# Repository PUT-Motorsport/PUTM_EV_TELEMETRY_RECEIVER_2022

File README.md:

# PUTM_EV_TELEMETRY_RECEIVER_2022

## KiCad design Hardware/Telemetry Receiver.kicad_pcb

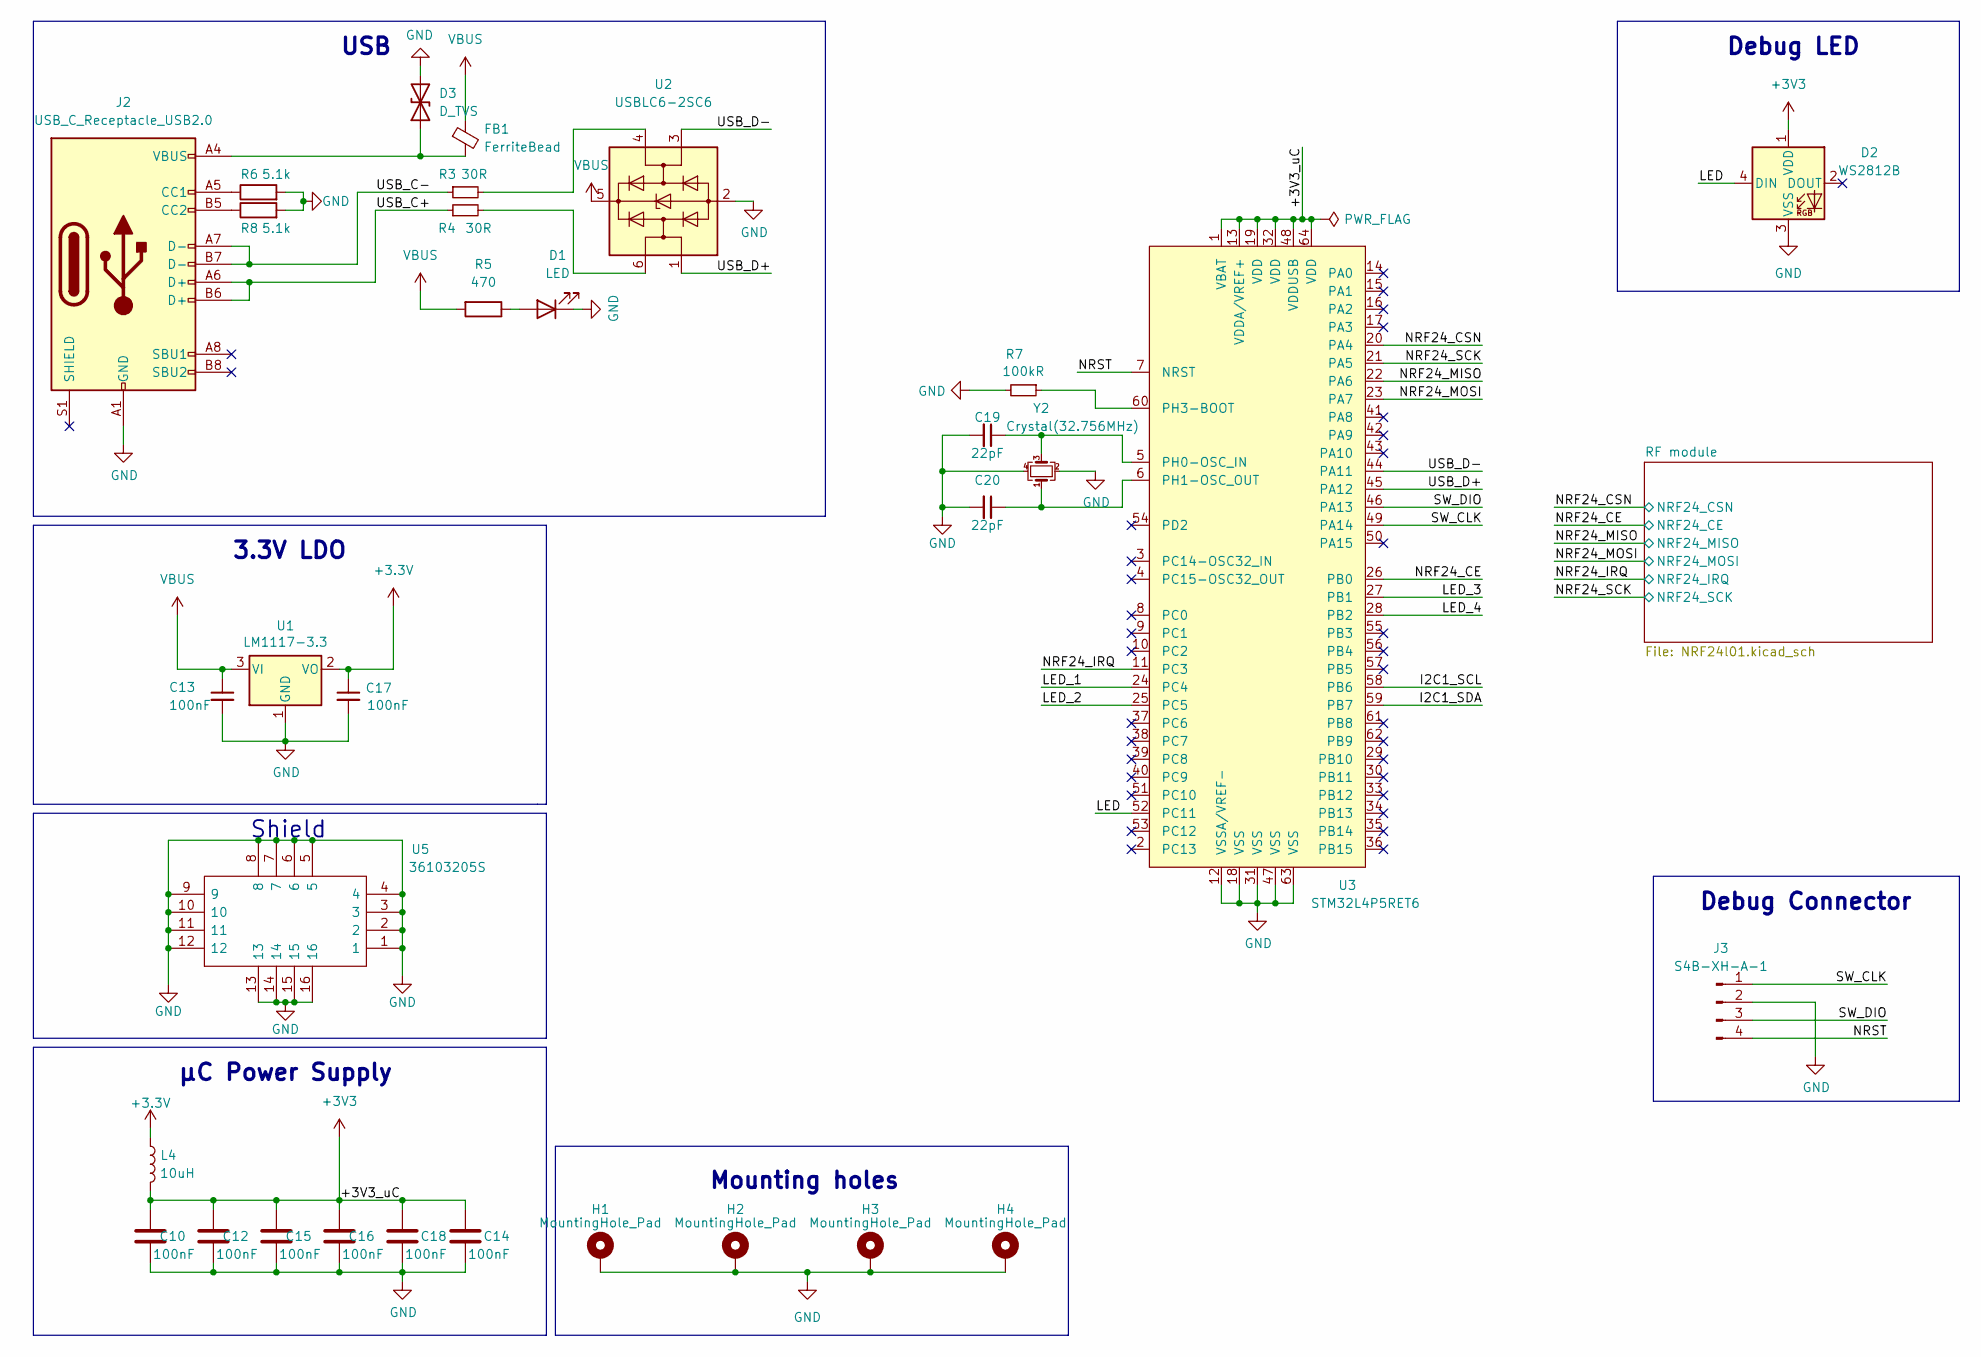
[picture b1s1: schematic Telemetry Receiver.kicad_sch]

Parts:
C10, C12, C13, C14, C15, C16, C17, C18: 100nF; C_0402_1005Metric
C19, C20: 22pF; C_0402_1005Metric; Manufacturer_Part_Number CBR04C220J5GACAUTO; Mouser Part Number 80-CBR04C220J5GAUTO
D1: LED; LED_0603_1608Metric
D2: WS2812B; LED_WS2812B_PLCC4_5.0x5.0mm_P3.2mm
D3: D_TVS; D_0402_1005Metric; Manufacturer_Part_Number LXES02TAA1-144; Mouser Part Number 81-LXES02TAA1-144
FB1: FerriteBead; R_0603_1608Metric; Manufacturer_Part_Number BLM18HE152SH1D; Mouser Part Number 81-BLM18HE152SH1D
H1, H2, H3, H4: MountingHole_Pad; MountingHole_3.2mm_M3_DIN965_Pad
J2: USB_C_Receptacle_USB2.0; USB_C_Receptacle_HRO_TYPE-C-31-M-12; Manufacturer_Part_Number USB4105-GF-A; Mouser Part Number 640-USB4105-GF-A
J3: S4B-XH-A-1; PinSocket_1x04_P2.54mm_Vertical
L4: 10uH; L_0402_1005Metric; Manufacturer_Part_Number LQW15DN100M00D; Mouser Part Number 81-LQW15DN100M00D
R3, R4: 30R; R_0402_1005Metric; Manufacturer_Part_Number 0402WGJ0300TCE; Mouser Part Number SMD0402-30R
R5: 470; R_0402_1005Metric; Manufacturer_Part_Number RN73H1ETTP4700B25; Mouser Part Number 660-RN73H1ETP4700B25
R6, R8: 5.1k; R_0402_1005Metric; Manufacturer_Part_Number RN73H1ETTP5101B25; Mouser Part Number 660-RN73H1ETP5101B25
R7: 100kR; R_0402_1005Metric; Manufacturer_Part_Number RN73H1ETTP1003B50; Mouser Part Number 660-RN73H1ETP1003B50
U1: LM1117-3.3; SOT-223-3_TabPin2
U2: USBLC6-2SC6; SOT-23-6; Manufacturer_Part_Number USBLC6-2SC6; Mouser Part Number USBLC6-2SC6
U3: STM32L4P5RET6
U5: 36103205S; Manufacturer_Part_Number 36103205S; Mouser Part Number 710-36103205S
Y2: Crystal(32.756MHz); Crystal_SMD_2520-4Pin_2.5x2.0mm; Manufacturer_Part_Number FH3200025; Mouser Part Number 729-FH3200025

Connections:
+3.3V: C17.1, L4.1, U1.2 (VO)
+3V3: C10.1, C12.1, C14.1, C15.1, C16.1, C18.1, D2.1 (VDD), L4.2, U3.1 (VBAT), U3.13 (VDDA/VREF+), U3.19 (VDD), U3.32 (VDD), U3.48 (VDDUSB), U3.64 (VDD); also elsewhere on the board
/I2C1_SCL: U3.58 (PB6)
/I2C1_SDA: U3.59 (PB7)
/LED: D2.4 (DIN), U3.52 (PC11)
/LED_1: U3.24 (PC4)
/LED_2: U3.25 (PC5)
/LED_3: U3.27 (PB1)
/LED_4: U3.28 (PB2)
/NRF24_CSN: U3.20 (PA4); also elsewhere on the board
/NRF24_IRQ: U3.11 (PC3); also elsewhere on the board
/NRF24_MISO: U3.22 (PA6); also elsewhere on the board
/NRF24_MOSI: U3.23 (PA7); also elsewhere on the board
/NRF24_SCK: U3.21 (PA5); also elsewhere on the board
/NRST: J3.4, U3.7 (NRST)
/SW_CLK: J3.1, U3.49 (PA14)
/SW_DIO: J3.3, U3.46 (PA13)
/USB_C+: J2.A6 (D+), J2.B6 (D+), R4.1
/USB_C-: J2.A7 (D-), J2.B7 (D-), R3.1
/USB_D+: U2.1 (I/O1), U3.45 (PA12)
/USB_D-: U2.3 (I/O2), U3.44 (PA11)
GND: C10.2, C12.2, C13.2, C14.2, C15.2, C16.2, C17.2, C18.2, C19.2, C20.2, D1.1 (K), D2.3 (VSS), D3.2 (A2), H1.1, H2.1, H3.1, H4.1, J2.A1 (GND), J2.A12 (GND), J2.B1 (GND), J2.B12 (GND), J3.2, R6.2, R7.2, R8.2, U1.1 (GND), U2.2 (GND), U3.12 (VSSA/VREF-), U3.18 (VSS), U3.31 (VSS), U3.47 (VSS), U3.63 (VSS), U5.1, U5.2, U5.3, U5.4, U5.5, U5.6, U5.7, U5.8, U5.9, U5.10, U5.11, U5.12, U5.13, U5.14, U5.15, U5.16, Y2.2, Y2.4; also elsewhere on the board
NRF24_CE: U3.26 (PB0); also elsewhere on the board
unnamed: C19.1, U3.5 (PH0-OSC_IN), Y2.3
unnamed: C20.1, U3.6 (PH1-OSC_OUT), Y2.1
unnamed: D1.2 (A), R5.1
unnamed: D3.1 (A1), FB1.2, J2.A4 (VBUS), J2.A9 (VBUS), J2.B4 (VBUS), J2.B9 (VBUS)
unnamed: J2.A5 (CC1), R6.1
unnamed: J2.B5 (CC2), R8.1
unnamed: R3.2, U2.4 (I/O2)
unnamed: R4.2, U2.6 (I/O1)
unnamed: R7.1, U3.60 (PH3-BOOT)
VBUS: C13.1, FB1.1, R5.2, U1.3 (VI), U2.5 (VBUS)

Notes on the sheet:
USB
3.3V LDO
Debug Connector
Mounting holes
Debug LED
µC Power Supply
Shield

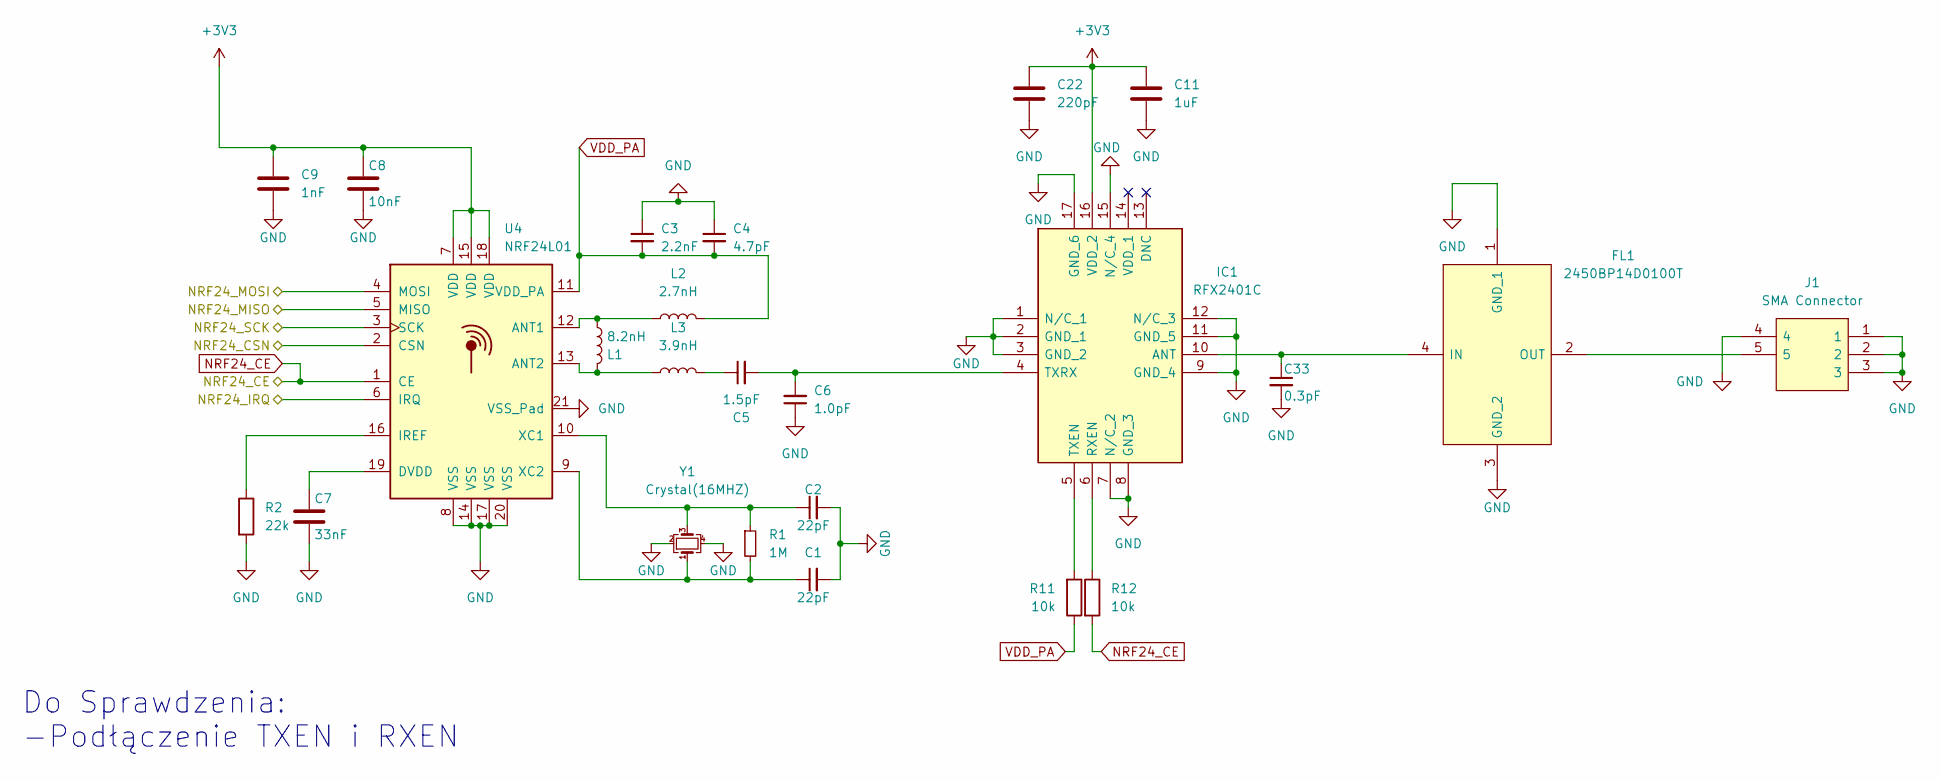
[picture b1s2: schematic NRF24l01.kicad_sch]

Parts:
C1, C2: 22pF; C_0402_1005Metric; Manufacturer_Part_Number CBR04C220J5GACAUTO; Mouser Part Number 80-CBR04C220J5GAUTO
C3: 2.2nF; C_0402_1005Metric; Manufacturer_Part_Number C0402C222J3TACAUTO; Mouser Part Number 80-C0402C222J3TAUTO
C4: 4.7pF; C_0402_1005Metric; Manufacturer_Part_Number CBR04C479B5GACAUTO; Mouser Part Number 80-CBR04C479B5GAUTO
C5: 1.5pF; C_0402_1005Metric; Manufacturer_Part_Number CBR04C159B5GACAUTO; Mouser Part Number 80-CBR04C159B5GAUTO
C6: 1.0pF; C_0402_1005Metric; Manufacturer_Part_Number CBR04C109B5GACAUTO; Mouser Part Number 80-CBR04C109B5GAUTO
C7: 33nF; C_0402_1005Metric; Manufacturer_Part_Number MAASU105SB7333MFCA01; Mouser Part Number 963-MAASU105SB7333MF
C8: 10nF; C_0402_1005Metric
C9: 1nF; C_0402_1005Metric; Manufacturer_Part_Number C0402C102J4GACAUTO; Mouser Part Number 80-C0402C102J4GCAUTO
C11: 1uF; C_0402_1005Metric
C22: 220pF; C_0402_1005Metric; Manufacturer_Part_Number C0402C221J4RACAUTO; Mouser Part Number 80-C0402C221J4RAUTO
C33: 0.3pF; C_0402_1005Metric; Manufacturer_Part_Number CBR04C308B5GACAUTO; Mouser Part Number 80-CBR04C308B5GAUTO
FL1: 2450BP14D0100T; Manufacturer_Part_Number 2450BP14D0100T; Mouser Part Number 609-2450BP14D0100T
IC1: RFX2401C; QFN50P300X300X60-17N-D; Manufacturer_Part_Number RFX2401C; Mouser Part Number 477-RFX2401C
J1: SMA Connector; 73251-2200; Manufacturer_Part_Number 73251-2201; Mouser Part Number 538-73251-2201
L1: 8.2nH; L_0402_1005Metric; Manufacturer_Part_Number MLG1005S8N2HT000; Mouser Part Number 810-MLG1005S8N2HT000
L2: 2.7nH; L_0402_1005Metric; Manufacturer_Part_Number MLG1005S2N7BTD25; Mouser Part Number 810-MLG1005S2N7BTD25
L3: 3.9nH; L_0402_1005Metric; Manufacturer_Part_Number MHQ1005P3N9CT000; Mouser Part Number 810-MHQ1005P3N9CT000
R1: 1M; R_0402_1005Metric; Manufacturer_Part_Number CQ02WGF1004TCE; Mouser Part Number CQ0402-1M-1%
R2: 22k; R_0402_1005Metric; Manufacturer_Part_Number AR02BTCY2202; Mouser Part Number AR0402-22K-0.1%
R11, R12: 10k; R_0402_1005Metric
U4: NRF24L01; QFN-20-1EP_3.5x3.5mm_P0.5mm_EP2x2mm_ThermalVias
Y1: Crystal(16MHZ); Crystal_SMD_2520-4Pin_2.5x2.0mm; Manufacturer_Part_Number 8Z-16.000MEEQ-T; Mouser Part Number 717-8Z-16.000MEEQ-T

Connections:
+3V3: C8.1, C9.1, C11.1, C22.1, IC1.16 (VDD_2), U4.7 (VDD), U4.15 (VDD), U4.18 (VDD); also elsewhere on the board
/NRF24_CSN: U4.2 (CSN); also elsewhere on the board
/NRF24_IRQ: U4.6 (IRQ); also elsewhere on the board
/NRF24_MISO: U4.5 (MISO); also elsewhere on the board
/NRF24_MOSI: U4.4 (MOSI); also elsewhere on the board
/NRF24_SCK: U4.3 (SCK); also elsewhere on the board
GND: C1.2, C2.2, C3.1, C4.1, C6.1, C7.2, C8.2, C9.2, C11.2, C22.2, C33.2, FL1.1 (GND_1), FL1.3 (GND_2), IC1.1 (N/C_1), IC1.2 (GND_1), IC1.3 (GND_2), IC1.7 (N/C_2), IC1.8 (GND_3), IC1.9 (GND_4), IC1.11 (GND_5), IC1.12 (N/C_3), IC1.15 (N/C_4), IC1.17 (GND_6), J1.1, J1.2, J1.3, J1.4, R2.2, U4.8 (VSS), U4.14 (VSS), U4.17 (VSS), U4.20 (VSS), U4.21 (VSS_Pad), Y1.2, Y1.4; also elsewhere on the board
NRF24_CE: R12.2, U4.1 (CE); also elsewhere on the board
unnamed: C1.1, R1.2, U4.9 (XC2), Y1.1
unnamed: C2.1, R1.1, U4.10 (XC1), Y1.3
unnamed: C5.1, L3.2
unnamed: C5.2, C6.2, IC1.4 (TXRX)
unnamed: C7.1, U4.19 (DVDD)
unnamed: C33.1, FL1.4 (IN), IC1.10 (ANT)
unnamed: FL1.2 (OUT), J1.5
unnamed: IC1.5 (TXEN), R11.2
unnamed: IC1.6 (RXEN), R12.1
unnamed: L1.1, L3.1, U4.13 (ANT2)
unnamed: L1.2, L2.1, U4.12 (ANT1)
unnamed: R2.1, U4.16 (IREF)
VDD_PA: C3.2, C4.2, L2.2, R11.1, U4.11 (VDD_PA)

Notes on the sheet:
Do Sprawdzenia: -Podłączenie TXEN i RXEN

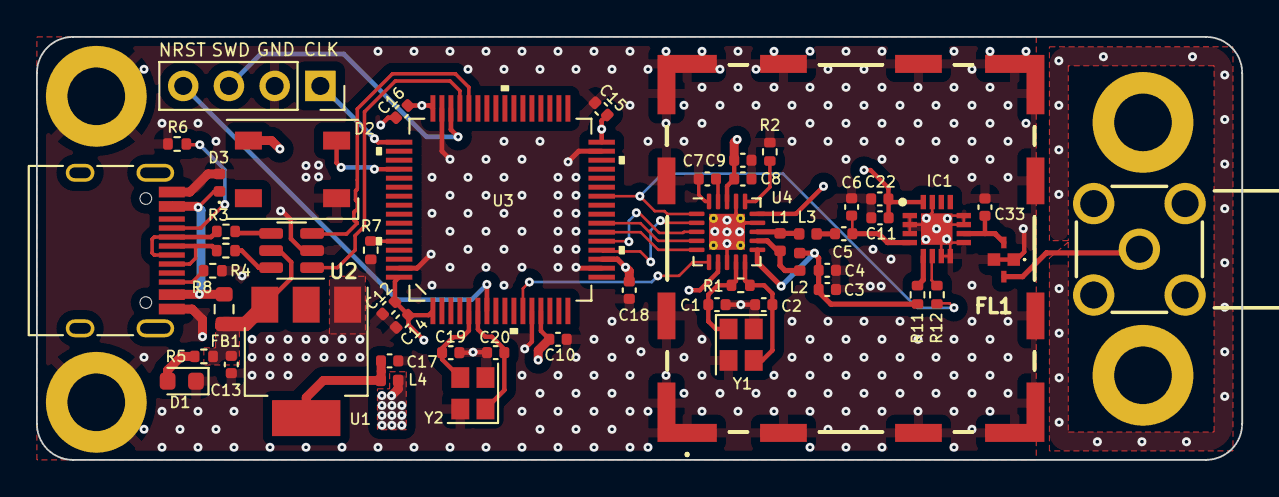
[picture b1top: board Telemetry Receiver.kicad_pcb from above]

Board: 4 copper layers, 67.0 x 23.5 mm, 56 parts (0 on the bottom side), 40 nets.

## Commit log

2022-10-07 Changed goldpin connector to micro usb
2022-10-07 Updating the deets
2022-10-17 4 layer PCB
2022-11-14 New 3d models
2022-11-24 USB C changes
2022-12-09 Signed board
2022-12-09 Added production files
2022-12-16 Changed footprint for available one
2023-01-23 Repo cleanups

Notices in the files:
parts and their libraries:
Copyright 2021 Accelerated Designs. All rights reserved.
